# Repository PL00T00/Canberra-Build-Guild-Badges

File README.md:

# Canberra-Build-Guild-Badges

PCB badges made for Build Guild Canberra. PCB's consist of a push button, LED, and resistor. Attendees will be soldering these and keeping them.

Quite an easy project to make but the idea took a while. Originally it was going to be a 555 chaser but I really wanted to focus on the simplest circuitry ever and make soldering easy.

## Assembly Instructions

To assemble you simple need to solder all tht components in their marked spots. The two testpoints on the bottom left of the board are for connecting flyends of a 9v battery snap, the red wire is positive and black is negative. Don't mess up the polaritiy!

## Materials Needed
- 1x PCB (This!)
- 1x 7mm push switch
- 1x 390 ohm resistor
- 1x LED
- 1x 9v Battery
- 1x 9v Battery snap connector

Here's a photo of the PCB!

Here's the 2d PCB

And here's the schematic

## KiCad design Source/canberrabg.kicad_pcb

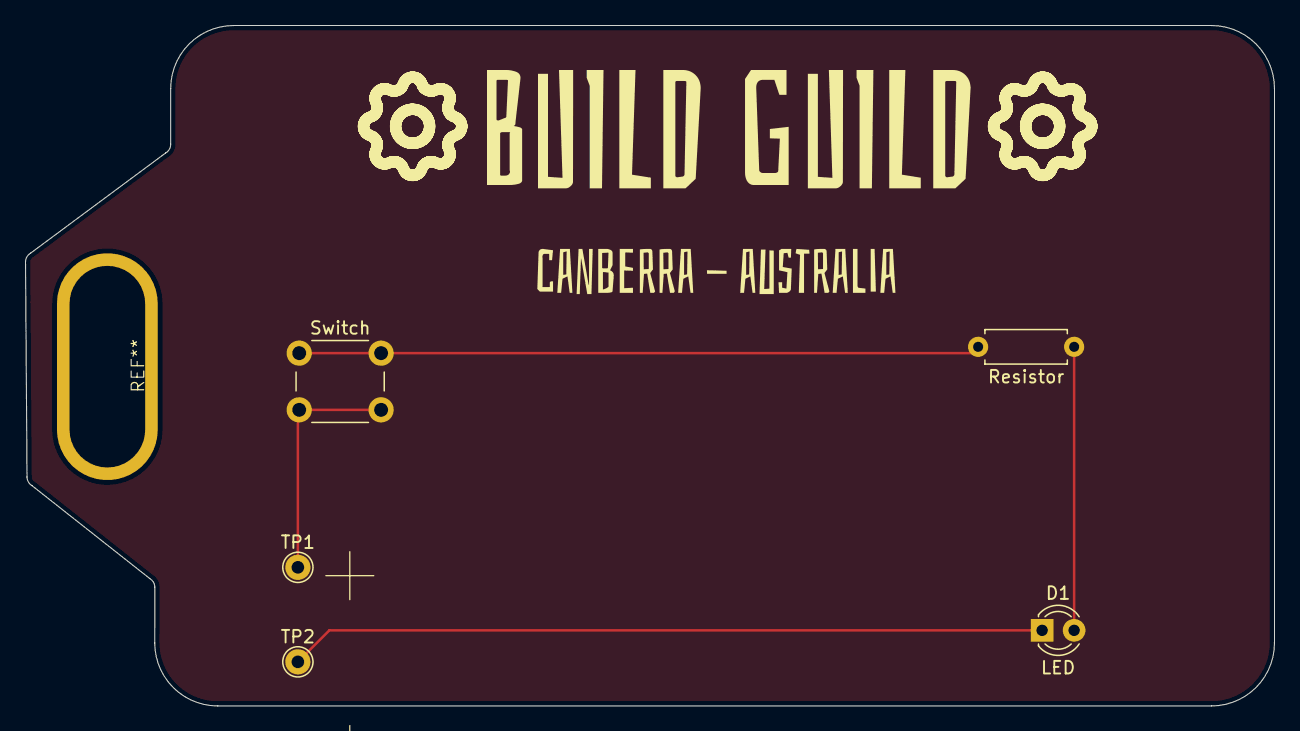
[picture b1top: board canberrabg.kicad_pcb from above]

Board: 2 copper layers, 99.1 x 54.0 mm, 5 parts (0 on the bottom side), 4 nets.

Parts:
D1: LED; LED_D3.0mm
Resistor: R; R_Axial_DIN0207_L6.3mm_D2.5mm_P7.62mm_Horizontal
Switch: SW_Push; SW_PUSH_6mm
TP1, TP2: TestPoint; TestPoint_THTPad_D2.0mm_Drill1.0mm

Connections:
unnamed: D1.2 (A), Resistor.1
unnamed: D1.1 (K), TP2.1 (1_1)
unnamed: Resistor.2, Switch.1
unnamed: Switch.2, TP1.1 (1_1)

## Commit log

2026-04-15 Create j
2026-04-15 Create d
2026-04-15 Update README with PCB badge description
    Added a brief description of the PCB badges.
2026-04-16 Update README with assembly instructions and materials
    Added detailed assembly instructions and materials needed for the PCB badges project.
2026-04-16 Create g
